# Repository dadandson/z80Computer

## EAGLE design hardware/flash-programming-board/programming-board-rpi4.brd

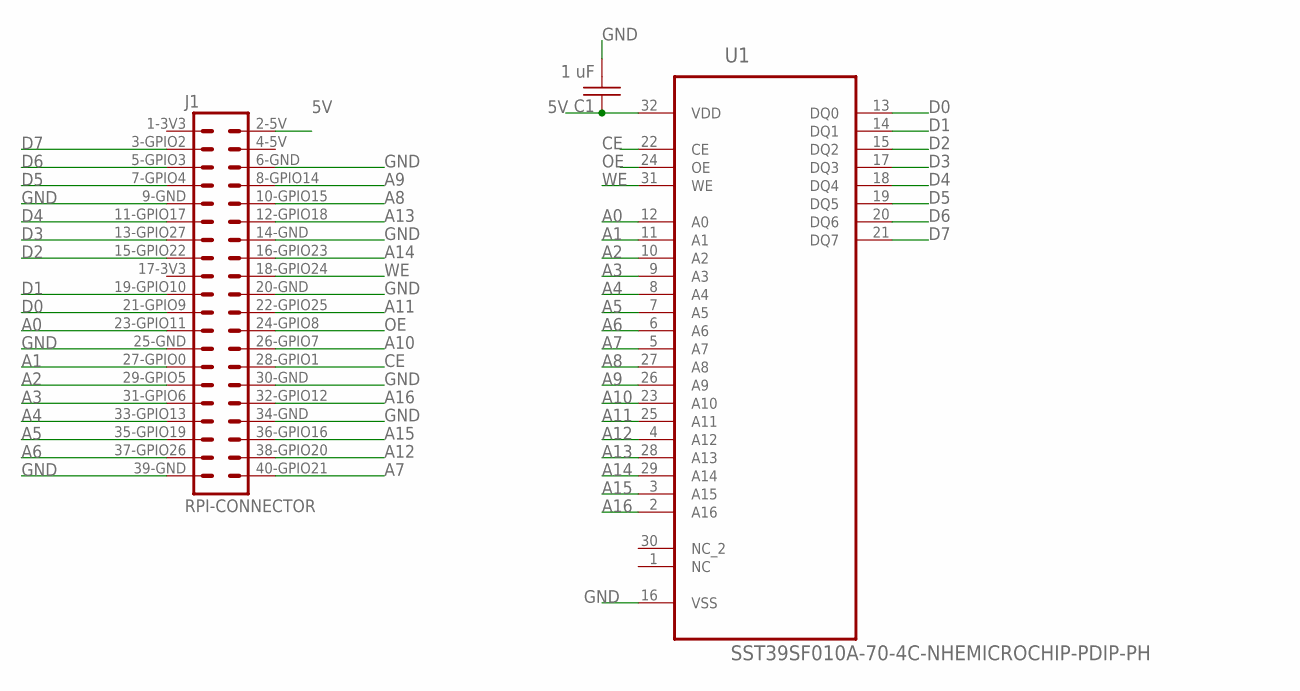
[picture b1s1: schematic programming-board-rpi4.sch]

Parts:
C1: 1 uF; C1206K
J1: RPI-CONNECTOR; RPI-2X20
U1: SST39SF010A-70-4C-NHEMICROCHIP-PDIP-PH; DIP1574W53P254L4191H508Q32B

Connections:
3V3: J1.1-3V3 (3V3), J1.17-3V3 (3V3)
5V: C1.1, J1.2-5V (5V), J1.4-5V (5V), U1.32 (VDD)
A0: J1.23-GPIO11 (GPIO11), U1.12 (A0)
A1: J1.27-GPIO0 (GPIO0), U1.11 (A1)
A2: J1.29-GPIO5 (GPIO5), U1.10 (A2)
A3: J1.31-GPIO6 (GPIO6), U1.9 (A3)
A4: J1.33-GPIO13 (GPIO13), U1.8 (A4)
A5: J1.35-GPIO19 (GPIO19), U1.7 (A5)
A6: J1.37-GPIO26 (GPIO26), U1.6 (A6)
A7: J1.40-GPIO21 (GPIO21), U1.5 (A7)
A8: J1.10-GPIO15 (GPIO15), U1.27 (A8)
A9: J1.8-GPIO14 (GPIO14), U1.26 (A9)
A10: J1.26-GPIO7 (GPIO7), U1.23 (A10)
A11: J1.22-GPIO25 (GPIO25), U1.25 (A11)
A12: J1.38-GPIO20 (GPIO20), U1.4 (A12)
A13: J1.12-GPIO18 (GPIO18), U1.28 (A13)
A14: J1.16-GPIO23 (GPIO23), U1.29 (A14)
A15: J1.36-GPIO16 (GPIO16), U1.3 (A15)
A16: J1.32-GPIO12 (GPIO12), U1.2 (A16)
CE: J1.28-GPIO1 (GPIO1), U1.22 (CE)
D0: J1.21-GPIO9 (GPIO9), U1.13 (DQ0)
D1: J1.19-GPIO10 (GPIO10), U1.14 (DQ1)
D2: J1.15-GPIO22 (GPIO22), U1.15 (DQ2)
D3: J1.13-GPIO27 (GPIO27), U1.17 (DQ3)
D4: J1.11-GPIO17 (GPIO17), U1.18 (DQ4)
D5: J1.7-GPIO4 (GPIO4), U1.19 (DQ5)
D6: J1.5-GPIO3 (GPIO3), U1.20 (DQ6)
D7: J1.3-GPIO2 (GPIO2), U1.21 (DQ7)
GND: C1.2, J1.6-GND (GND), J1.9-GND (GND), J1.14-GND (GND), J1.20-GND (GND), J1.25-GND (GND), J1.30-GND (GND), J1.34-GND (GND), J1.39-GND (GND), U1.16 (VSS)
OE: J1.24-GPIO8 (GPIO8), U1.24 (OE)
WE: J1.18-GPIO24 (GPIO24), U1.31 (WE)

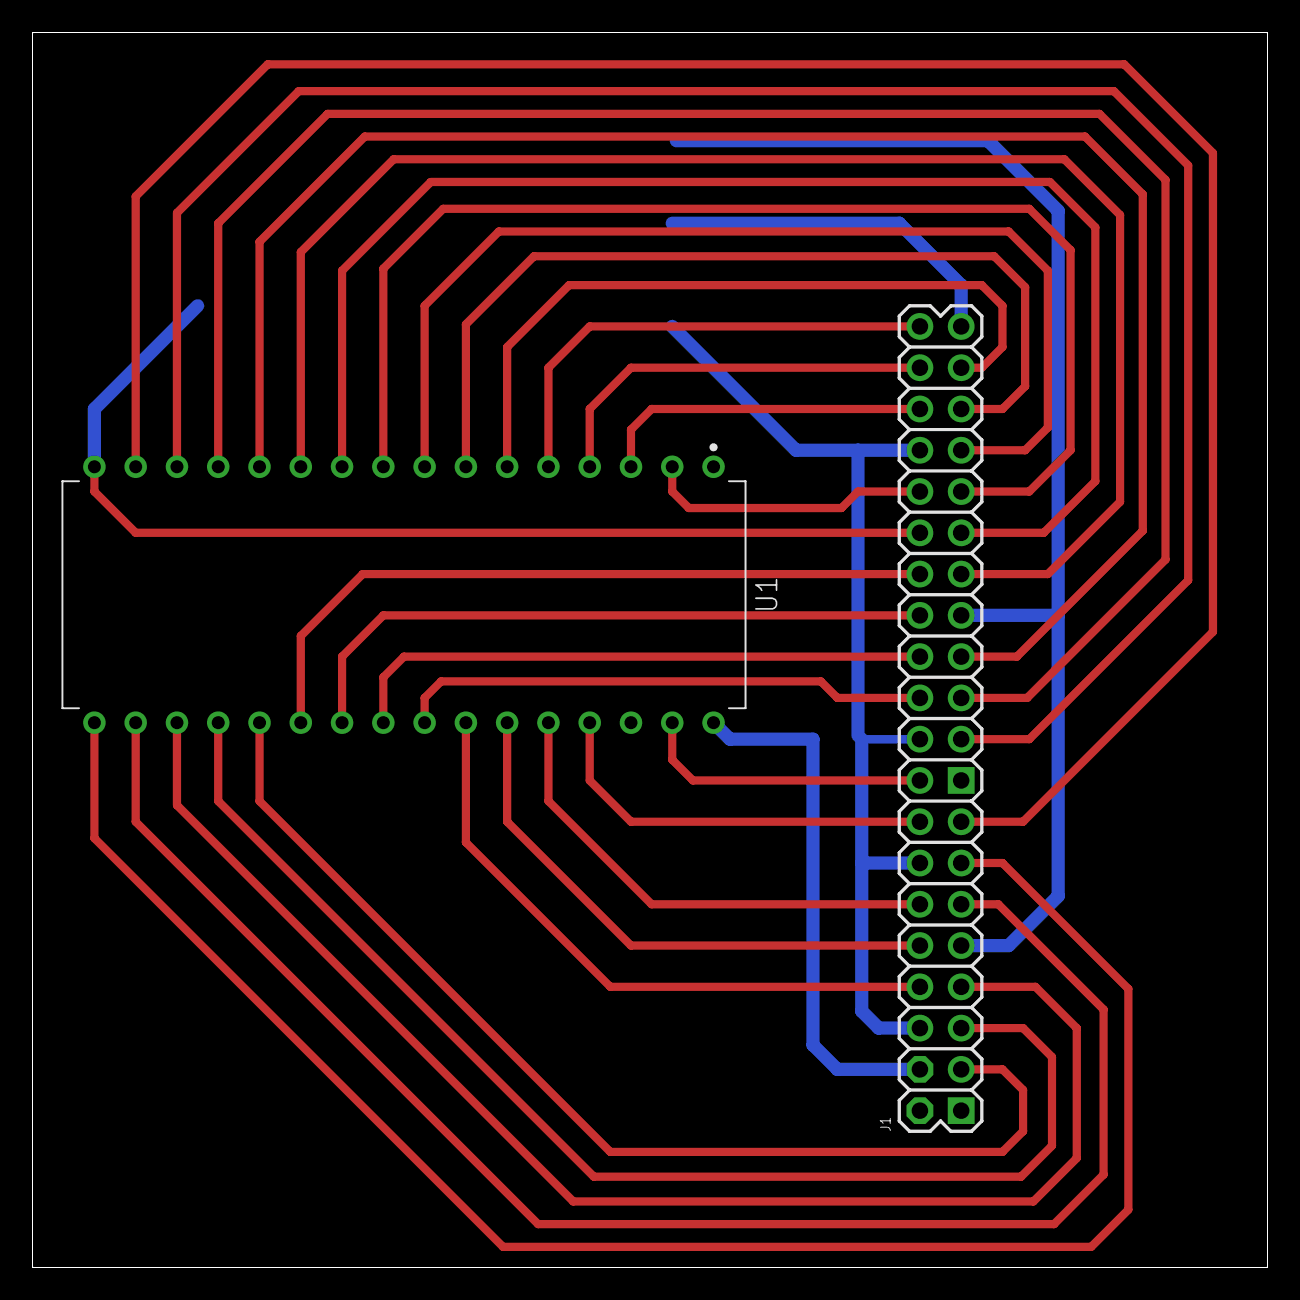
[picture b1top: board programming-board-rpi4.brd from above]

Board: 2 copper layers, 76.0 x 76.0 mm, 3 parts (1 on the bottom side), 31 nets.

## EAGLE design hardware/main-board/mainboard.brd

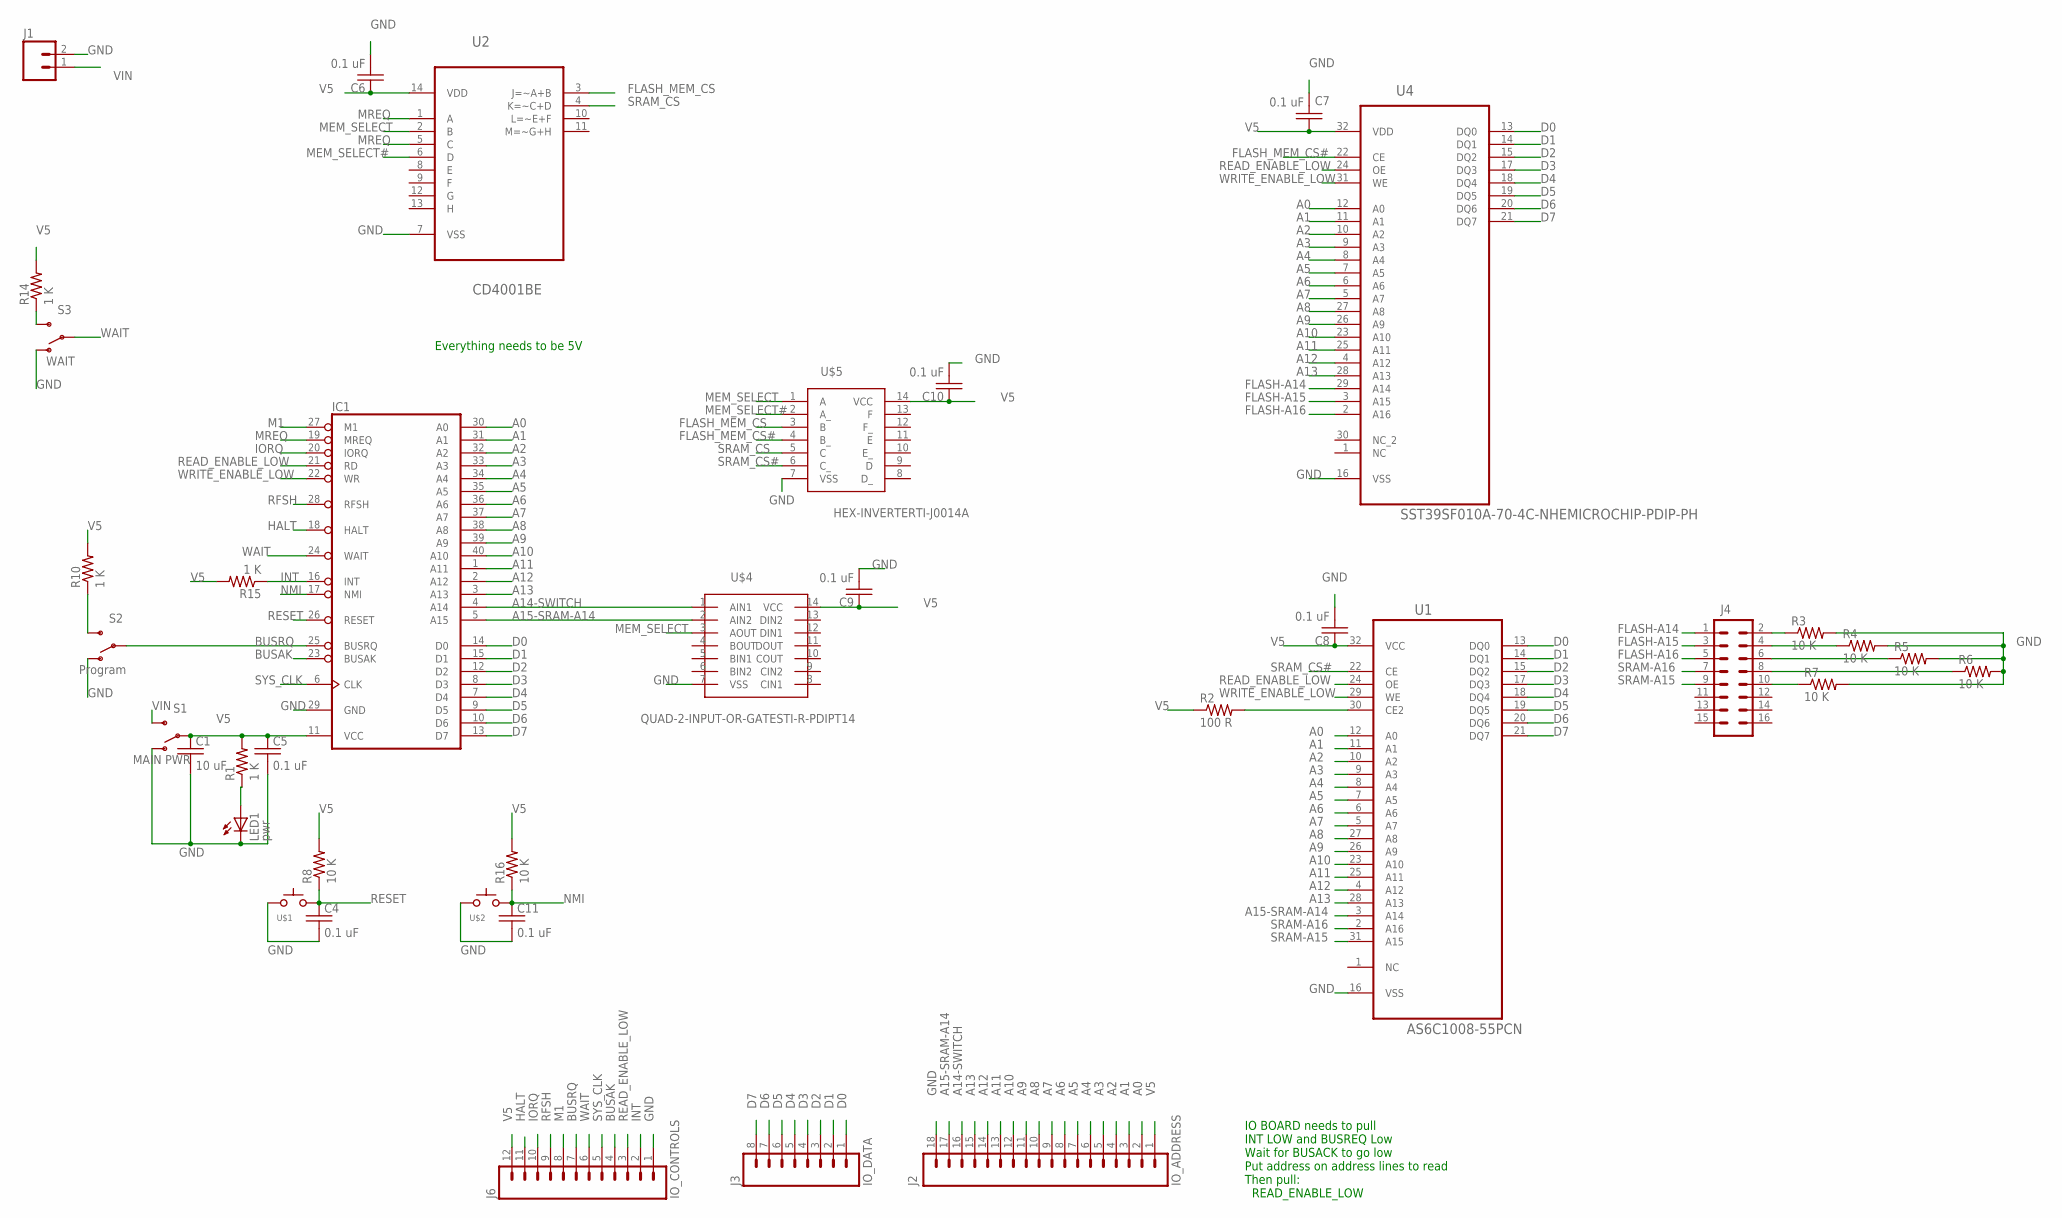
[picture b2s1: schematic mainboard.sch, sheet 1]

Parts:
C1: 10 uF; C0805K
C4, C5, C6, C7, C8, C9, C10, C11: 0.1 uF; C0805K
IC1: Z80CPU; DIL40
J1: M02PTH; 1X02
J2: IO_ADDRESS; 1X18
J3: IO_DATA; 1X08_LOCK_LONGPADS
J4: M08X2; 2X8
J6: IO_CONTROLS; 1X12_LONGPADS
LED1: pwr; LED-1206
R1, R10, R14, R15: 1 K; 0805
R2: 100 R; 0805
R3, R4, R5, R6, R7, R8, R16: 10 K; 0805
S1: MAIN PWR; SWITCH-SPDT_KIT
S2: Program; SWITCH-SPDT_KIT
S3: WAIT; SWITCH-SPDT_KIT
U1: AS6C1008-55PCN; DIP254P1524X393-32
U2: CD4001BE; DIP254P762X508-14
U4: SST39SF010A-70-4C-NHEMICROCHIP-PDIP-PH; DIP1574W53P254L4191H508Q32B
U$1, U$2: SWITCH_TACTILETACTILE-2PIN-NARROW; TACTILE-2PIN-NARROW
U$4: QUAD-2-INPUT-OR-GATESTI-R-PDIPT14; DIP762W36P254L1981H508Q14B
U$5: HEX-INVERTERTI-J0014A; DIP797W66P254L1954H508Q14B

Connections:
A0: IC1.30 (A0), J2.2, U1.12 (A0), U4.12 (A0)
A1: IC1.31 (A1), J2.3, U1.11 (A1), U4.11 (A1)
A2: IC1.32 (A2), J2.4, U1.10 (A2), U4.10 (A2)
A3: IC1.33 (A3), J2.5, U1.9 (A3), U4.9 (A3)
A4: IC1.34 (A4), J2.6, U1.8 (A4), U4.8 (A4)
A5: IC1.35 (A5), J2.7, U1.7 (A5), U4.7 (A5)
A6: IC1.36 (A6), J2.8, U1.6 (A6), U4.6 (A6)
A7: IC1.37 (A7), J2.9, U1.5 (A7), U4.5 (A7)
A8: IC1.38 (A8), J2.10, U1.27 (A8), U4.27 (A8)
A9: IC1.39 (A9), J2.11, U1.26 (A9), U4.26 (A9)
A10: IC1.40 (A10), J2.12, U1.23 (A10), U4.23 (A10)
A11: IC1.1 (A11), J2.13, U1.25 (A11), U4.25 (A11)
A12: IC1.2 (A12), J2.14, U1.4 (A12), U4.4 (A12)
A13: IC1.3 (A13), J2.15, U1.28 (A13), U4.28 (A13)
A14-SWITCH: IC1.4 (A14), J2.16, U$4.1 (AIN1)
A15-SRAM-A14: IC1.5 (A15), J2.17, U1.3 (A14), U$4.2 (AIN2)
BUSAK: IC1.23 (BUSAK), J6.4
BUSRQ: IC1.25 (BUSRQ), J6.7, S2.2
D0: IC1.14 (D0), J3.1, U1.13 (DQ0), U4.13 (DQ0)
D1: IC1.15 (D1), J3.2, U1.14 (DQ1), U4.14 (DQ1)
D2: IC1.12 (D2), J3.3, U1.15 (DQ2), U4.15 (DQ2)
D3: IC1.8 (D3), J3.4, U1.17 (DQ3), U4.17 (DQ3)
D4: IC1.7 (D4), J3.5, U1.18 (DQ4), U4.18 (DQ4)
D5: IC1.9 (D5), J3.6, U1.19 (DQ5), U4.19 (DQ5)
D6: IC1.10 (D6), J3.7, U1.20 (DQ6), U4.20 (DQ6)
D7: IC1.13 (D7), J3.8, U1.21 (DQ7), U4.21 (DQ7)
FLASH-A14: J4.1, U4.29 (A14)
FLASH-A15: J4.3, U4.3 (A15)
FLASH-A16: J4.5, U4.2 (A16)
FLASH_MEM_CS: U2.3 (J=~A+B), U$5.3 (B)
FLASH_MEM_CS#: U4.22 (CE), U$5.4 (B_)
GND: C1.2, C4.2, C5.2, C6.2, C7.2, C8.2, C9.2, C10.2, C11.2, IC1.29 (GND), J1.2, J2.18, J6.1, LED1.C, R3.2, R4.2, R5.2, R6.2, R7.2, S1.1 (O), S2.1 (O), S3.1 (O), U1.16 (VSS), U2.7 (VSS), U4.16 (VSS), U$1.P$2 (C), U$2.P$2 (C), U$4.7 (VSS), U$5.7 (VSS)
HALT: IC1.18 (HALT), J6.11
INT: IC1.16 (INT), J6.2, R15.1
IORQ: IC1.20 (IORQ), J6.10
M1: IC1.27 (M1), J6.8
MEM_SELECT: U2.2 (B), U$4.3 (AOUT), U$5.1 (A)
MEM_SELECT#: U2.6 (D), U$5.2 (A_)
MREQ: IC1.19 (MREQ), U2.1 (A), U2.5 (C)
unnamed: LED1.A, R1.1
unnamed: R10.1, S2.3 (S)
unnamed: R2.2, U1.30 (CE2)
unnamed: J4.2, R3.1
unnamed: J4.4, R4.1
unnamed: J4.6, R5.1
unnamed: J4.8, R6.1
unnamed: J4.10, R7.1
unnamed: R14.1, S3.3 (S)
NMI: C11.1, IC1.17 (NMI), R16.1, U$2.P$1 (A)
READ_ENABLE_LOW: IC1.21 (RD), J6.3, U1.24 (OE), U4.24 (OE)
RESET: C4.1, IC1.26 (RESET), R8.1, U$1.P$1 (A)
RFSH: IC1.28 (RFSH), J6.9
SRAM-A15: J4.9, U1.31 (A15)
SRAM-A16: J4.7, U1.2 (A16)
SRAM_CS: U2.4 (K=~C+D), U$5.5 (C)
SRAM_CS#: U1.22 (CE), U$5.6 (C_)
SYS_CLK: IC1.6 (CLK), J6.5
V5: C1.1, C5.1, C6.1, C7.1, C8.1, C9.1, C10.1, IC1.11 (VCC), J2.1, J6.12, R1.2, R2.1, R8.2, R10.2, R14.2, R15.2, R16.2, S1.2, U1.32 (VCC), U2.14 (VDD), U4.32 (VDD), U$4.14 (VCC), U$5.14 (VCC)
VIN: J1.1, S1.3 (S)
WAIT: IC1.24 (WAIT), J6.6, S3.2
WRITE_ENABLE_LOW: IC1.22 (WR), U1.29 (WE), U4.31 (WE)

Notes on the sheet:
Everything needs to be 5V
IO BOARD needs to pull INT LOW and BUSREQ Low Wait for BUSACK to go low Put address on address lines to read Then pull: READ_ENABLE_LOW

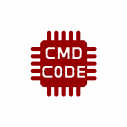
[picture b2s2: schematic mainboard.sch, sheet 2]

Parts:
U$3: CMD_C0DE_LOGOCMD_CODE_LOGO_SILK; CMD_C0DE_LOGO_SILK

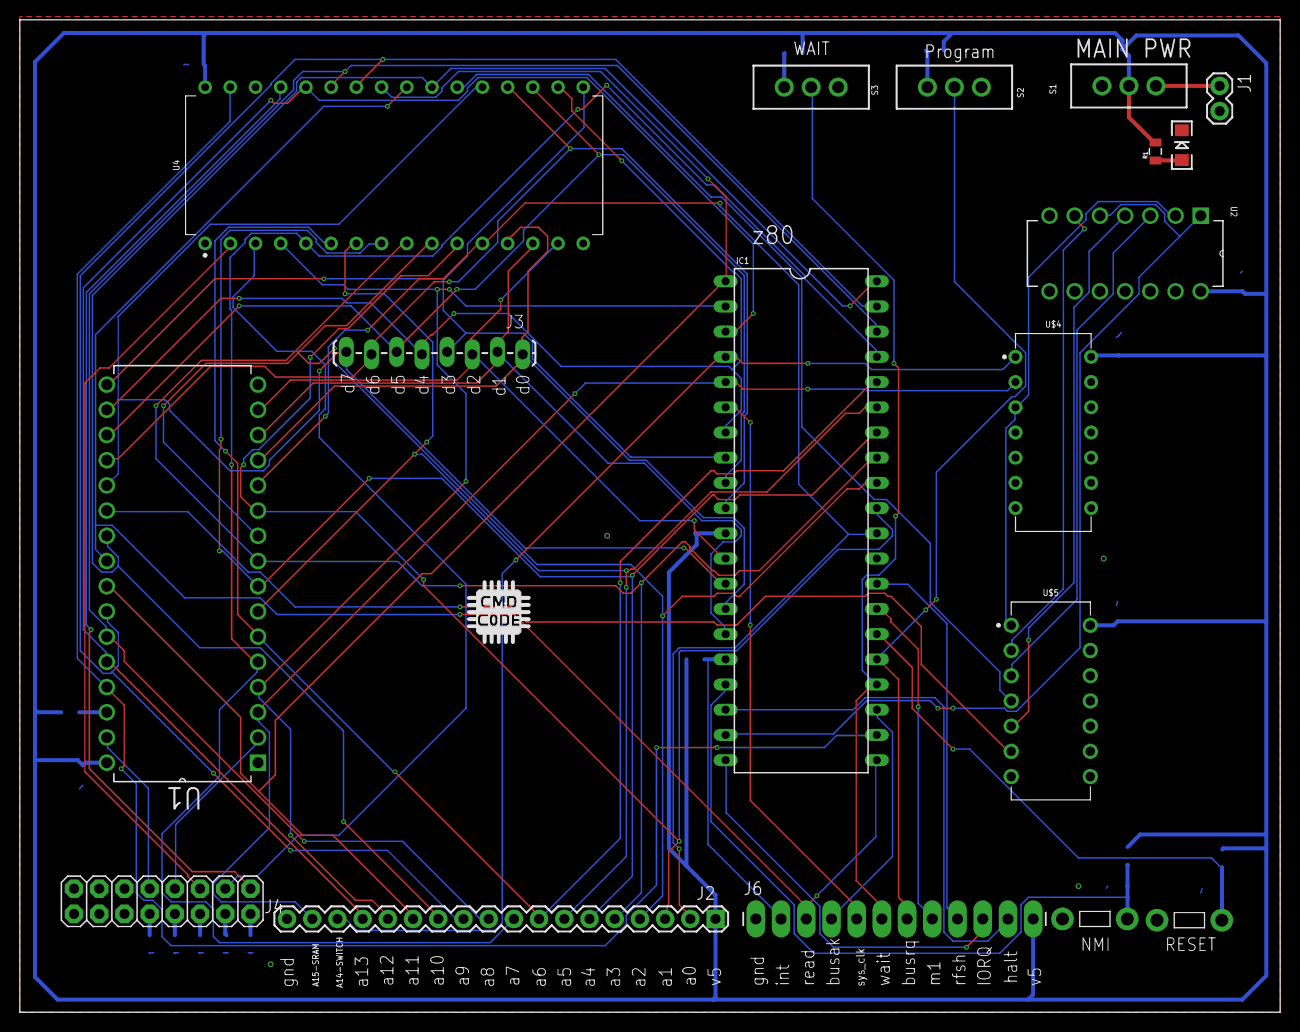
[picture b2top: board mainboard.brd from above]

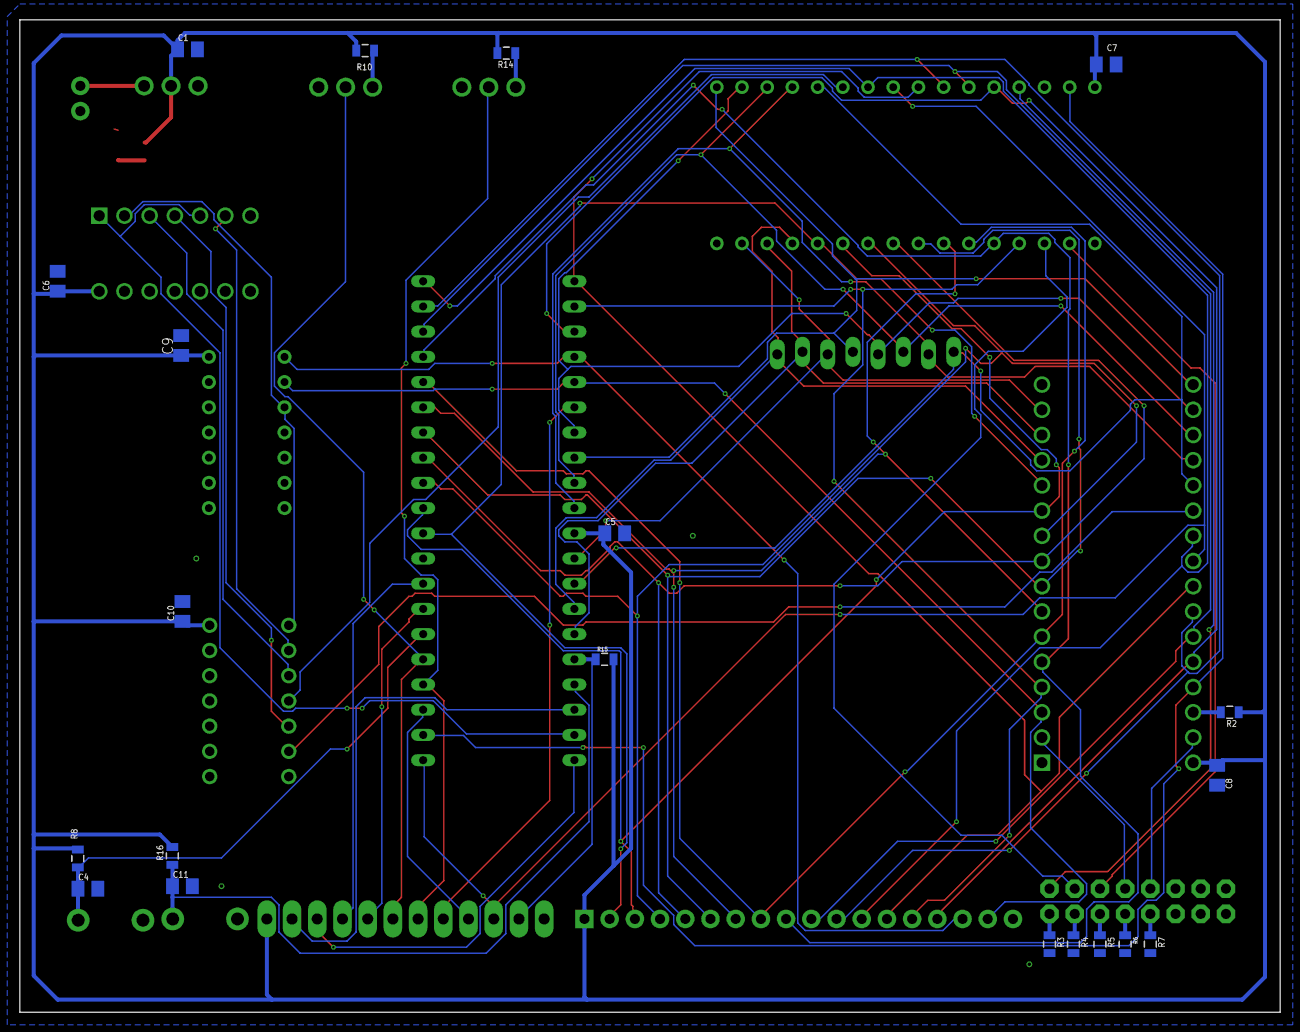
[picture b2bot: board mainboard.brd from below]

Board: 2 copper layers, 127.0 x 100.0 mm, 39 parts (20 on the bottom side), 61 nets.

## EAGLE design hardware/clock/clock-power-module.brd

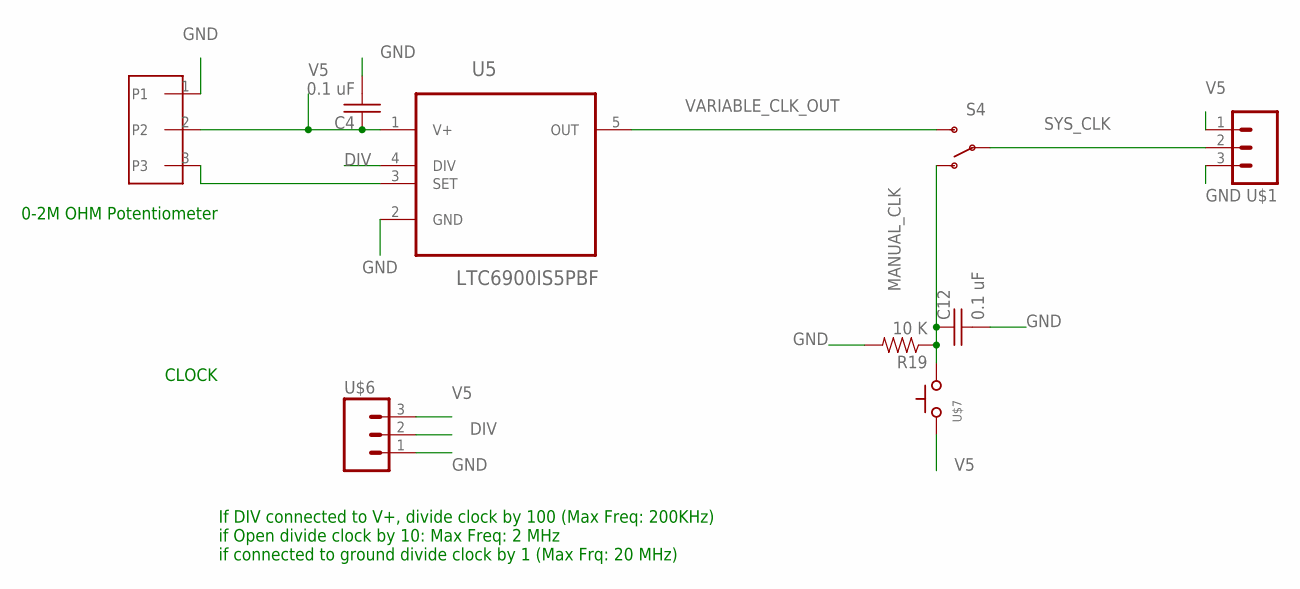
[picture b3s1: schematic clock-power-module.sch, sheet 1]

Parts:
C4, C12: 0.1 uF; C0805K
R19: 10 K; 0805
S4: SWITCH-SPSTKIT; SWITCH-SPDT_KIT
U5: LTC6900IS5PBF; SOT95P280X100-5N
U$1, U$6: M03; 1X03_UDPI
U$3: POTENTIOMETER; SCREW-TERM-EP
U$7: SWITCH_TACTILETACTILE-2PIN-NARROW; TACTILE-2PIN-NARROW

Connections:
DIV: U5.4 (DIV), U$6.2
GND: C4.2, C12.2, R19.2, U5.2 (GND), U$1.3, U$3.1, U$6.1; also elsewhere on the board
MANUAL_CLK: C12.1, R19.1, S4.1 (O), U$7.P$1 (A)
unnamed: U5.3 (SET), U$3.3
SYS_CLK: S4.2, U$1.2
V5: C4.1, U5.1 (V+), U$1.1, U$3.2, U$6.3, U$7.P$2 (C); also elsewhere on the board
VARIABLE_CLK_OUT: S4.3 (S), U5.5 (OUT)

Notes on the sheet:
CLOCK
0-2M OHM Potentiometer
If DIV connected to V+, divide clock by 100 (Max Freq: 200KHz) if Open divide clock by 10: Max Freq: 2 MHz if connected to ground divide clock by 1 (Max Frq: 20 MHz)

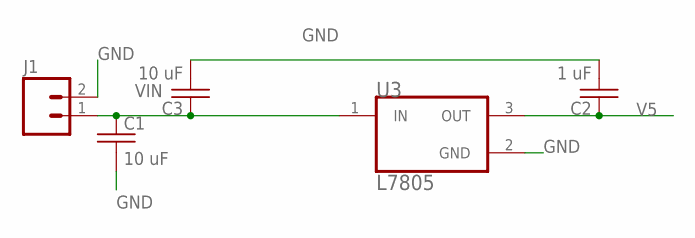
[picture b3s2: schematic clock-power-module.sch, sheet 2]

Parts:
C1, C3: 10 uF; C0805K
C2: 1 uF; C0805K
J1: M02PTH3; 1X02_LONGPADS
U3: L7805; TO-220-3

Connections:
GND: C1.2, C2.2, C3.2, J1.2, U3.2 (GND); also elsewhere on the board
V5: C2.1, U3.3 (OUT); also elsewhere on the board
VIN: C1.1, C3.1, J1.1, U3.1 (IN)

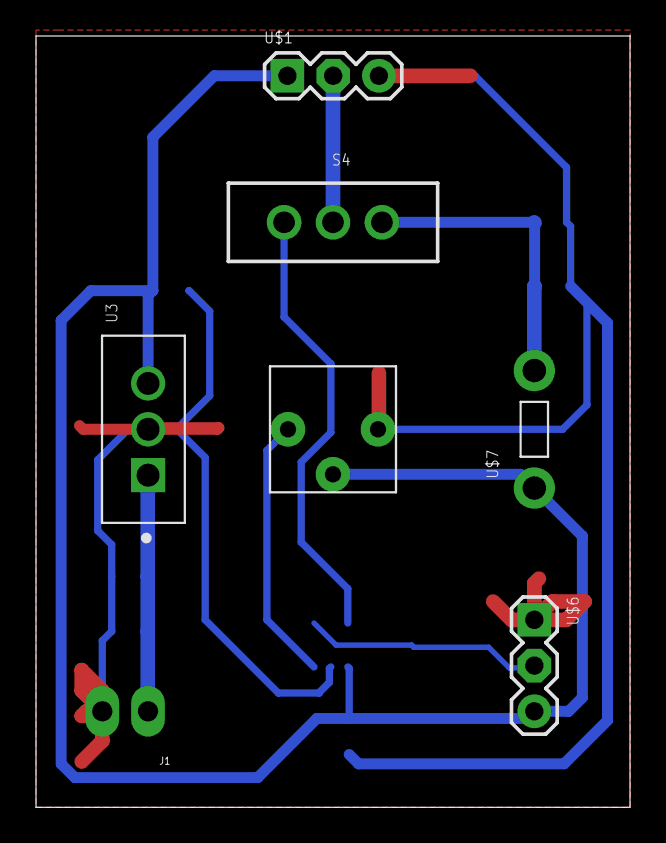
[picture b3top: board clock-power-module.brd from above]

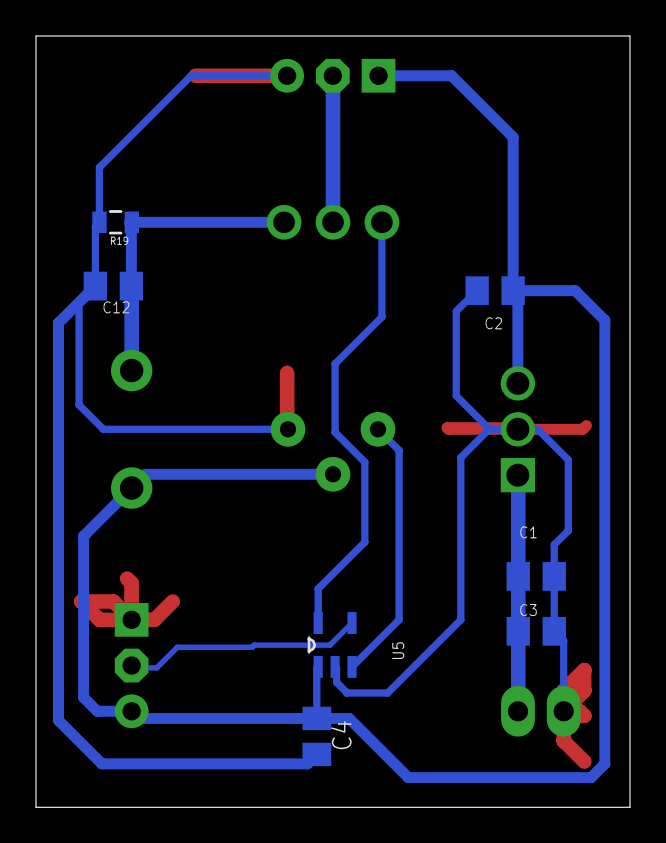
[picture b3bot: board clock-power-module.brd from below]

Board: 2 copper layers, 33.0 x 42.9 mm, 14 parts (7 on the bottom side), 8 nets.

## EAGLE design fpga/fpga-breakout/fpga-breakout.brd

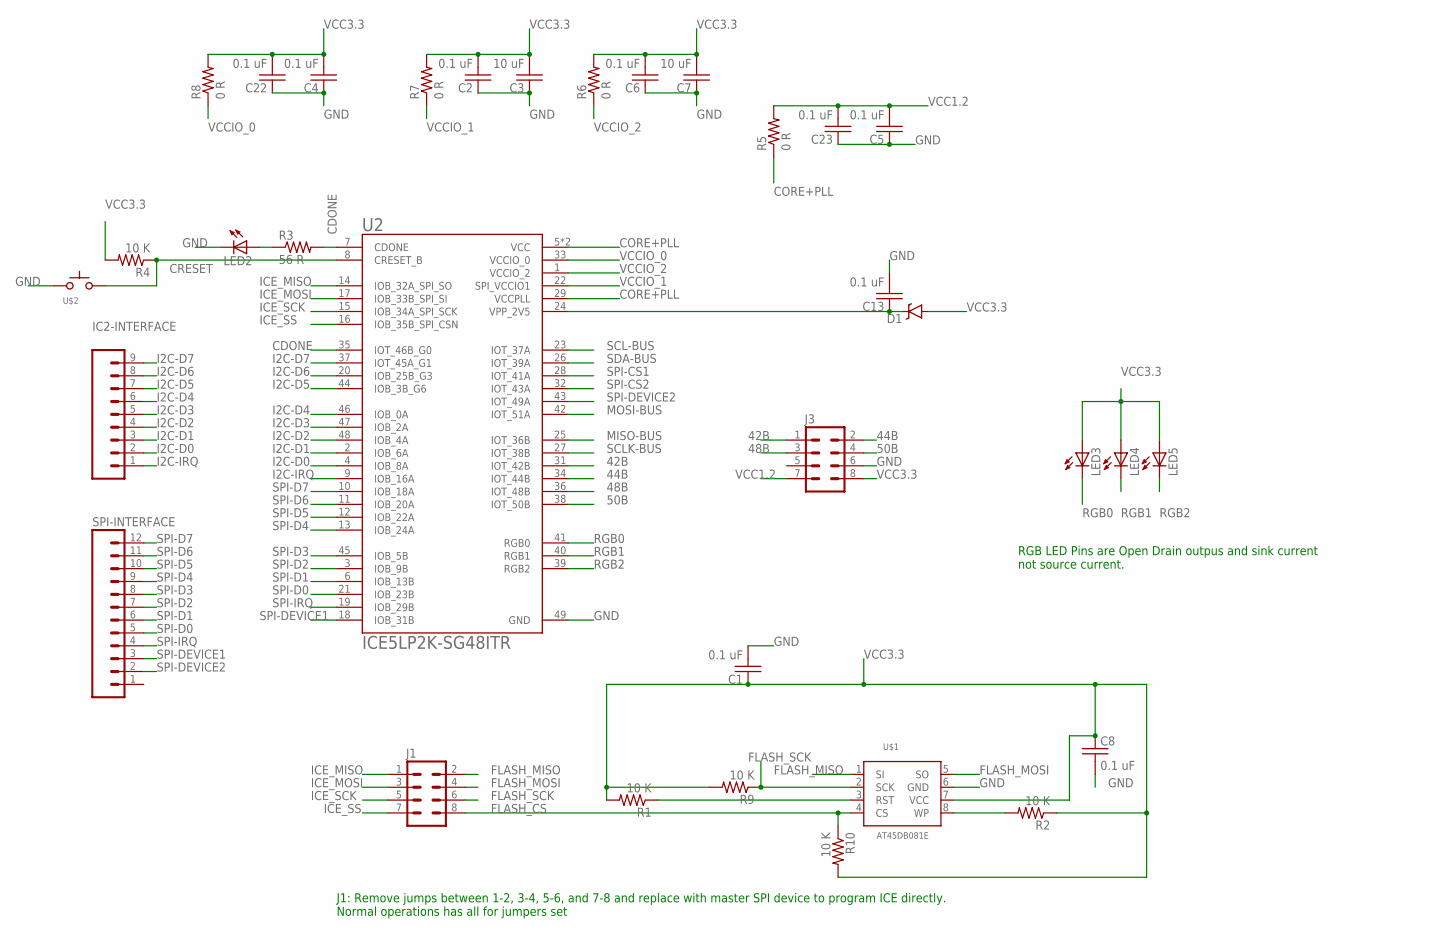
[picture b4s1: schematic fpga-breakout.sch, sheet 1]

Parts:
C1, C2, C4, C5, C6, C8, C13, C22, C23: 0.1 uF; C0603
C3, C7: 10 uF; C0603
D1: DIODE-SCHOTTKYDIOAD-TH; DIOAD1060W80L520D270
IC2-INTERFACE: M09; 1X09
J1, J3: M04X2; 2X4
LED2: LED1206; LED-1206
LED3, LED4, LED5: LED3MM
R1, R2, R4, R9, R10: 10 K; 0805
R3: 56 R; 1206
R5, R6, R7, R8: 0 R; 0805
SPI-INTERFACE: M12PTH; 1X12
U2: ICE5LP2K-SG48ITR; QFN50P700X700X100-49N
U$1: AT45DB8081E; SOIC127P600X175-8N
U$2: SWITCH_TACTILETACTILE-2PIN-NARROW; TACTILE-2PIN-NARROW

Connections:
42B: J3.1, U2.31 (IOT_42B)
44B: J3.2, U2.34 (IOT_44B)
48B: J3.3, U2.36 (IOT_48B)
50B: J3.4, U2.38 (IOT_50B)
CDONE: R3.2, U2.7 (CDONE), U2.35 (IOT_46B_G0)
CORE+PLL: R5.1, U2.5 (VCC), U2.29 (VCCPLL), U2.30 (VCC)
CRESET: R4.1, U2.8 (CRESET_B), U$2.P$1 (A)
FLASH_CS: J1.8, R10.1, U$1.4 (CS)
FLASH_MISO: J1.2, U$1.1 (SI)
FLASH_MOSI: J1.4, U$1.5 (SO)
FLASH_SCK: J1.6, R9.1, U$1.2 (SCK)
GND: C1.2, C2.1, C3.1, C4.1, C5.1, C6.1, C7.1, C8.2, C13.2, C22.1, C23.1, J3.6, LED2.C, U2.49 (GND), U$1.6 (GND), U$2.P$2 (C); also elsewhere on the board
I2C-D0: IC2-INTERFACE.2, U2.4 (IOB_8A)
I2C-D1: IC2-INTERFACE.3, U2.2 (IOB_6A)
I2C-D2: IC2-INTERFACE.4, U2.48 (IOB_4A)
I2C-D3: IC2-INTERFACE.5, U2.47 (IOB_2A)
I2C-D4: IC2-INTERFACE.6, U2.46 (IOB_0A)
I2C-D5: IC2-INTERFACE.7, U2.44 (IOB_3B_G6)
I2C-D6: IC2-INTERFACE.8, U2.20 (IOB_25B_G3)
I2C-D7: IC2-INTERFACE.9, U2.37 (IOT_45A_G1)
I2C-IRQ: IC2-INTERFACE.1, U2.9 (IOB_16A)
ICE_MISO: J1.1, U2.14 (IOB_32A_SPI_SO)
ICE_MOSI: J1.3, U2.17 (IOB_33B_SPI_SI)
ICE_SCK: J1.5, U2.15 (IOB_34A_SPI_SCK)
ICE_SS: J1.7, U2.16 (IOB_35B_SPI_CSN)
MISO-BUS: U2.25 (IOT_36B); also elsewhere on the board
MOSI-BUS: U2.42 (IOT_51A); also elsewhere on the board
unnamed: LED2.A, R3.1
unnamed: R1.1, U$1.3 (RST)
unnamed: C13.1, D1.C, U2.24 (VPP_2V5)
unnamed: R2.2, U$1.8 (WP)
RGB0: LED3.K (C), U2.41 (RGB0)
RGB1: LED4.K (C), U2.40 (RGB1)
RGB2: LED5.K (C), U2.39 (RGB2)
SCL-BUS: U2.23 (IOT_37A); also elsewhere on the board
SCLK-BUS: U2.27 (IOT_38B); also elsewhere on the board
SDA-BUS: U2.26 (IOT_39A); also elsewhere on the board
SPI-CS1: U2.28 (IOT_41A); also elsewhere on the board
SPI-CS2: U2.32 (IOT_43A); also elsewhere on the board
SPI-D0: SPI-INTERFACE.5, U2.21 (IOB_23B)
SPI-D1: SPI-INTERFACE.6, U2.6 (IOB_13B)
SPI-D2: SPI-INTERFACE.7, U2.3 (IOB_9B)
SPI-D3: SPI-INTERFACE.8, U2.45 (IOB_5B)
SPI-D4: SPI-INTERFACE.9, U2.13 (IOB_24A)
SPI-D5: SPI-INTERFACE.10, U2.12 (IOB_22A)
SPI-D6: SPI-INTERFACE.11, U2.11 (IOB_20A)
SPI-D7: SPI-INTERFACE.12, U2.10 (IOB_18A)
SPI-DEVICE1: SPI-INTERFACE.3, U2.18 (IOB_31B)
SPI-DEVICE2: SPI-INTERFACE.2, U2.43 (IOT_49A)
SPI-IRQ: SPI-INTERFACE.4, U2.19 (IOB_29B)
VCC1.2: C5.2, C23.2, J3.7, R5.2; also elsewhere on the board
VCC3.3: C1.1, C2.2, C3.2, C4.2, C6.2, C7.2, C8.1, C22.2, D1.A, J3.8, LED3.A, LED4.A, LED5.A, R1.2, R2.1, R4.2, R6.2, R7.2, R8.2, R9.2, R10.2, U$1.7 (VCC); also elsewhere on the board
VCCIO_0: R8.1, U2.33 (VCCIO_0)
VCCIO_1: R7.1, U2.22 (SPI_VCCIO1)
VCCIO_2: R6.1, U2.1 (VCCIO_2)

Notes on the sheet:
RGB LED Pins are Open Drain outpus and sink current not source current.
J1: Remove jumps between 1-2, 3-4, 5-6, and 7-8 and replace with master SPI device to program ICE directly. Normal operations has all for jumpers set

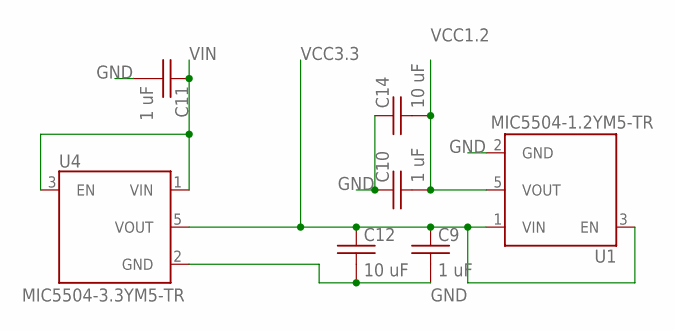
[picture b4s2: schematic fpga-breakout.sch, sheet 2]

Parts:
C9, C10, C11: 1 uF; C0603
C12, C14: 10 uF; C0603
U1: MIC5504-1.2YM5-TR; SOT23-5P95_280X145XL45X37N
U4: MIC5504-3.3YM5-TR; SOT23-5P95_280X145XL45X37N

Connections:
GND: C9.2, C10.1, C11.2, C12.2, C14.1, U1.2 (GND), U4.2 (GND); also elsewhere on the board
VCC1.2: C10.2, C14.2, U1.5 (VOUT); also elsewhere on the board
VCC3.3: C9.1, C12.1, U1.1 (VIN), U1.3 (EN), U4.5 (VOUT); also elsewhere on the board
VIN: C11.1, U4.1 (VIN), U4.3 (EN)

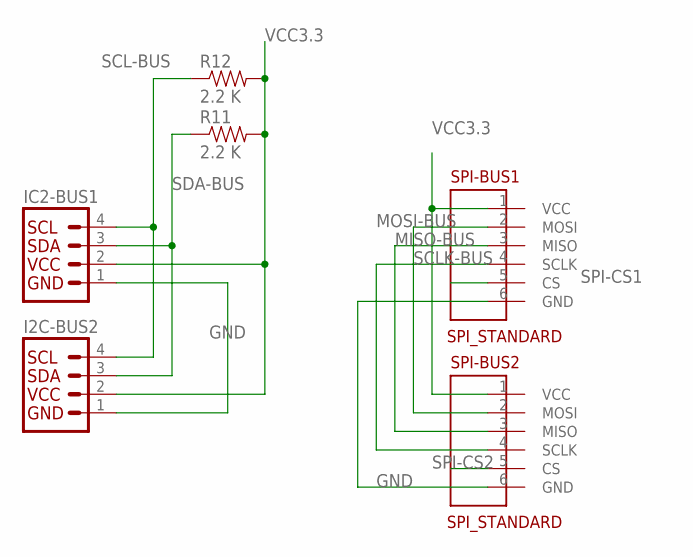
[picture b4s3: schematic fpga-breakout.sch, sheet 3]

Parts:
I2C-BUS2: I2C_STANDARD; 1X04
IC2-BUS1: I2C_STANDARD; 1X04
R11, R12: 2.2 K; 0805
SPI-BUS1, SPI-BUS2: SPI_STANDARD; 1X06

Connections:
GND: I2C-BUS2.1, IC2-BUS1.1, SPI-BUS1.6 (GND), SPI-BUS2.6 (GND); also elsewhere on the board
MISO-BUS: SPI-BUS1.3 (MISO), SPI-BUS2.3 (MISO); also elsewhere on the board
MOSI-BUS: SPI-BUS1.2 (MOSI), SPI-BUS2.2 (MOSI); also elsewhere on the board
SCL-BUS: I2C-BUS2.4, IC2-BUS1.4, R12.1; also elsewhere on the board
SCLK-BUS: SPI-BUS1.4 (SCLK), SPI-BUS2.4 (SCLK); also elsewhere on the board
SDA-BUS: I2C-BUS2.3, IC2-BUS1.3, R11.1; also elsewhere on the board
SPI-CS1: SPI-BUS1.5 (CS); also elsewhere on the board
SPI-CS2: SPI-BUS2.5 (CS); also elsewhere on the board
VCC3.3: I2C-BUS2.2, IC2-BUS1.2, R11.2, R12.2, SPI-BUS1.1 (VCC), SPI-BUS2.1 (VCC); also elsewhere on the board

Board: 2 copper layers, 46 parts (0 on the bottom side), 56 nets, no tracks yet.

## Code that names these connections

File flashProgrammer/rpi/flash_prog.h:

/*
 * J8:
   3V3  (1) (2)  5V
 GPIO2  (3) (4)  5V
 GPIO3  (5) (6)  GND
 GPIO4  (7) (8)  GPIO14
   GND  (9) (10) GPIO15
GPIO17 (11) (12) GPIO18
GPIO27 (13) (14) GND
GPIO22 (15) (16) GPIO23
   3V3 (17) (18) GPIO24
GPIO10 (19) (20) GND
 GPIO9 (21) (22) GPIO25
GPIO11 (23) (24) GPIO8
   GND (25) (26) GPIO7
 GPIO0 (27) (28) GPIO1
 GPIO5 (29) (30) GND
 GPIO6 (31) (32) GPIO12
GPIO13 (33) (34) GND
GPIO19 (35) (36) GPIO16
GPIO26 (37) (38) GPIO20
   GND (39) (40) GPIO21
*/

#include <pigpio.h>

static const uint8_t F_A0=11;
static const uint8_t F_A1=0;
static const uint8_t F_A2=5;
static const uint8_t F_A3=6;
static const uint8_t F_A4=13;
static const uint8_t F_A5=19;
static const uint8_t F_A6=26;
static const uint8_t F_A7=21;
static const uint8_t F_A8=15;
static const uint8_t F_A9=14;
static const uint8_t F_A10=7;
static const uint8_t F_A11=25;
static const uint8_t F_A12=20;
static const uint8_t F_A13=18;
static const uint8_t F_A14=23;
static const uint8_t F_A15=16;
static const uint8_t F_A16=12;


static const uint8_t F_D0=9;
static const uint8_t F_D1=10;
static const uint8_t F_D2=22;
static const uint8_t F_D3=27;
static const uint8_t F_D4=17;
static const uint8_t F_D5=4;
static const uint8_t F_D6=3;
static const uint8_t F_D7=2;

static const uint8_t CE=1;
static const uint8_t WE=24;
static const uint8_t OE=8;

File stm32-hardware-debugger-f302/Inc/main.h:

/* USER CODE BEGIN Header */
/**
  ******************************************************************************
  * @file           : main.h
  * @brief          : Header for main.c file.
  *                   This file contains the common defines of the application.
  ******************************************************************************
  * @attention
  *
  * <h2><center>&copy; Copyright (c) 2020 STMicroelectronics.
  * All rights reserved.</center></h2>
  *
  * This software component is licensed by ST under BSD 3-Clause license,
  * the "License"; You may not use this file except in compliance with the
  * License. You may obtain a copy of the License at:
  *                        opensource.org/licenses/BSD-3-Clause
  *
  ******************************************************************************
  */
/* USER CODE END Header */

/* Define to prevent recursive inclusion -------------------------------------*/
#ifndef __MAIN_H
#define __MAIN_H

#ifdef __cplusplus
extern "C" {
#endif

/* Includes ------------------------------------------------------------------*/
#include "stm32f3xx_hal.h"

/* Private includes ----------------------------------------------------------*/
/* USER CODE BEGIN Includes */

/* USER CODE END Includes */

/* Exported types ------------------------------------------------------------*/
/* USER CODE BEGIN ET */

/* USER CODE END ET */

/* Exported constants --------------------------------------------------------*/
/* USER CODE BEGIN EC */

/* USER CODE END EC */

/* Exported macro ------------------------------------------------------------*/
/* USER CODE BEGIN EM */

/* USER CODE END EM */

/* Exported functions prototypes ---------------------------------------------*/
void Error_Handler(void);

/* USER CODE BEGIN EFP */


/* USER CODE END EFP */

/* Private defines -----------------------------------------------------------*/
#define DATA3_Pin GPIO_PIN_13
#define DATA3_GPIO_Port GPIOC
#define Z80CLK_INT_Pin GPIO_PIN_0
#define Z80CLK_INT_GPIO_Port GPIOC
#define Z80CLK_INT_EXTI_IRQn EXTI0_IRQn
#define DATA4_Pin GPIO_PIN_1
#define DATA4_GPIO_Port GPIOC
#define DATA5_Pin GPIO_PIN_2
#define DATA5_GPIO_Port GPIOC
#define DATA6_Pin GPIO_PIN_3
#define DATA6_GPIO_Port GPIOC
#define ADDR0_Pin GPIO_PIN_0
#define ADDR0_GPIO_Port GPIOA
#define ADDR1_Pin GPIO_PIN_1
#define ADDR1_GPIO_Port GPIOA
#define USART_TX_Pin GPIO_PIN_2
#define USART_TX_GPIO_Port GPIOA
#define USART_RX_Pin GPIO_PIN_3
#define USART_RX_GPIO_Port GPIOA
#define ADDR2_Pin GPIO_PIN_4
#define ADDR2_GPIO_Port GPIOA
#define ADDR3_Pin GPIO_PIN_5
#define ADDR3_GPIO_Port GPIOA
#define ADDR4_Pin GPIO_PIN_6
#define ADDR4_GPIO_Port GPIOA
#define ADDR5_Pin GPIO_PIN_7
#define ADDR5_GPIO_Port GPIOA
#define DATA7_Pin GPIO_PIN_4
#define DATA7_GPIO_Port GPIOC
#define M1_Pin GPIO_PIN_5
#define M1_GPIO_Port GPIOC
#define ADDR11_Pin GPIO_PIN_0
#define ADDR11_GPIO_Port GPIOB
#define ADDR12_Pin GPIO_PIN_1
#define ADDR12_GPIO_Port GPIOB
#define ADDR13_Pin GPIO_PIN_2
#define ADDR13_GPIO_Port GPIOB
#define ADDR14_Pin GPIO_PIN_10
#define ADDR14_GPIO_Port GPIOB
#define ADDR15_Pin GPIO_PIN_11
#define ADDR15_GPIO_Port GPIOB
#define DATA0_Pin GPIO_PIN_12
#define DATA0_GPIO_Port GPIOB
#define GREEN_LED_Pin GPIO_PIN_13
#define GREEN_LED_GPIO_Port GPIOB
#define DATA1_Pin GPIO_PIN_14
#define DATA1_GPIO_Port GPIOB
#define DATA2_Pin GPIO_PIN_15
#define DATA2_GPIO_Port GPIOB
#define MREQ_Pin GPIO_PIN_6
#define MREQ_GPIO_Port GPIOC
#define IORQ_Pin GPIO_PIN_7
#define IORQ_GPIO_Port GPIOC
#define RD_Pin GPIO_PIN_8
#define RD_GPIO_Port GPIOC
#define WR_Pin GPIO_PIN_9
#define WR_GPIO_Port GPIOC
#define ADDR6_Pin GPIO_PIN_8
#define ADDR6_GPIO_Port GPIOA
#define ADDR7_Pin GPIO_PIN_9
#define ADDR7_GPIO_Port GPIOA
#define ADDR8_Pin GPIO_PIN_10
#define ADDR8_GPIO_Port GPIOA
#define ADDR9_Pin GPIO_PIN_11
#define ADDR9_GPIO_Port GPIOA
#define ADDR10_Pin GPIO_PIN_12
#define ADDR10_GPIO_Port GPIOA
#define TMS_Pin GPIO_PIN_13
#define TMS_GPIO_Port GPIOA
#define TCK_Pin GPIO_PIN_14
#define TCK_GPIO_Port GPIOA
#define BUSAK_Pin GPIO_PIN_15
#define BUSAK_GPIO_Port GPIOA
#define INT_Pin GPIO_PIN_2
#define INT_GPIO_Port GPIOD
#define SWO_Pin GPIO_PIN_3
#define SWO_GPIO_Port GPIOB
#define BUSRQ_Pin GPIO_PIN_4
#define BUSRQ_GPIO_Port GPIOB
#define NMI_Pin GPIO_PIN_5
#define NMI_GPIO_Port GPIOB
#define WAIT_Pin GPIO_PIN_8
#define WAIT_GPIO_Port GPIOB
/* USER CODE BEGIN Private defines */

/* USER CODE END Private defines */

#ifdef __cplusplus
}
#endif

#endif /* __MAIN_H */

/************************ (C) COPYRIGHT STMicroelectronics *****END OF FILE****/

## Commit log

2020-01-02 docker ready
2020-01-10 better name
2020-01-16 adding notes
2020-01-16 notes
2020-01-18 added fuse
2020-01-21 initial check in of schema and test fpga stuff
2020-01-21 remove temp files
2020-01-30 adding clock and power module
2020-01-30 closer to layout complete for z80Computer
2020-02-01 main board starting to route
2020-02-02 update on clock board, so much cleaner now re-layout of main board
2020-02-02 some routing complete
2020-02-16 not sure
2020-02-16 adding svg
2020-02-16 only pads this time
2020-02-16 now only pads
2020-03-04 adding basic project files
2020-03-07 compiles
2020-03-07 basic debuger code working
2021-01-03 start of programmer for flash
2021-01-03 adding programmer for flash chip
2021-01-03 increased size of traces
2021-01-04 closer
2021-01-04 made the board slightly smaller so I can mill out of fr4
